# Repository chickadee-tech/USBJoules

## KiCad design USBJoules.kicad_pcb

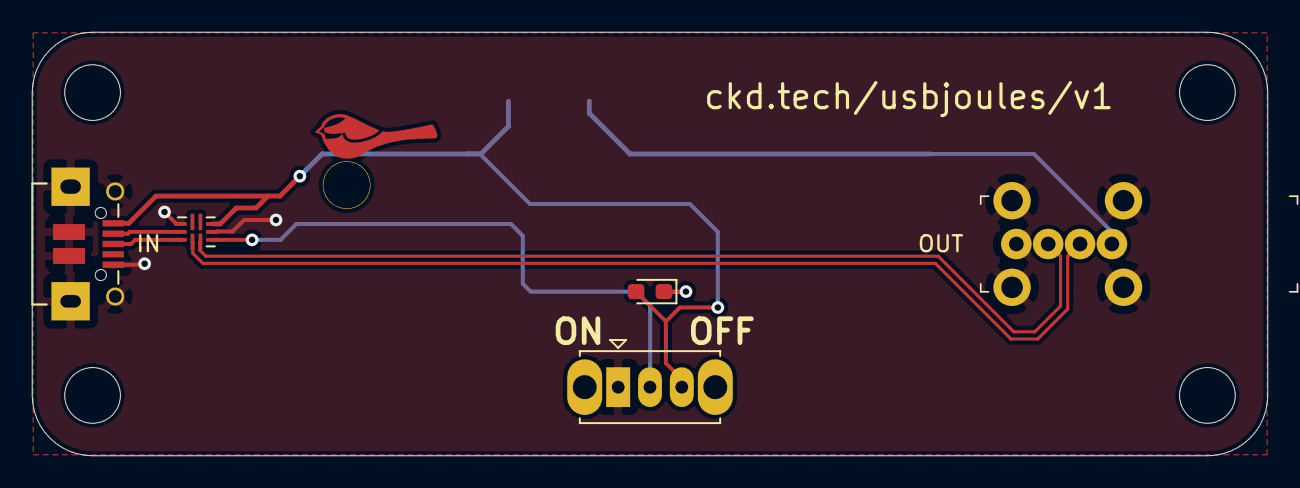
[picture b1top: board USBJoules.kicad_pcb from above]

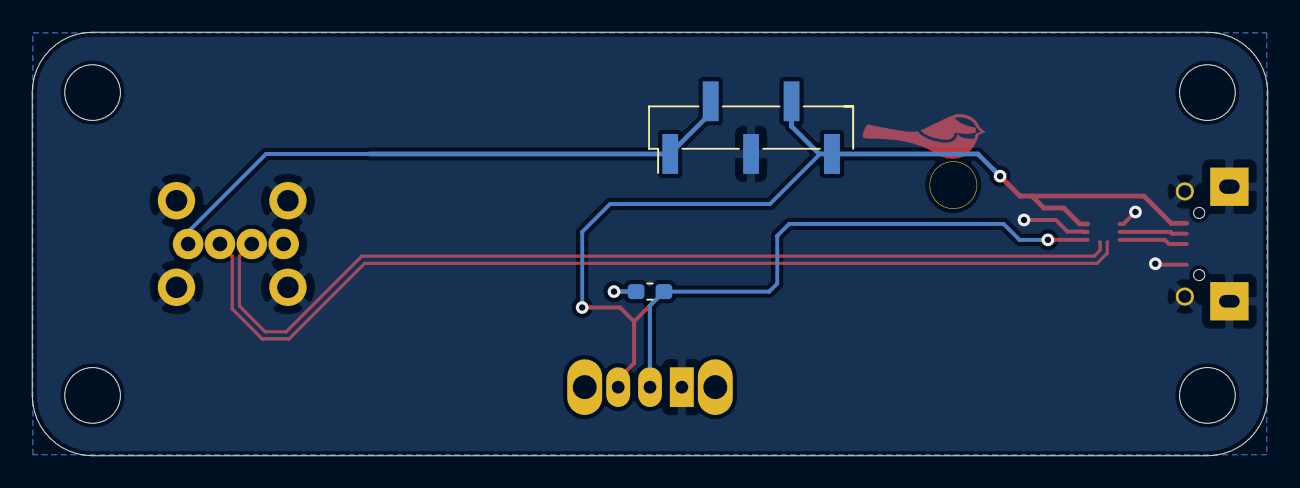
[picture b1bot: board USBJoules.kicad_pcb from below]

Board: 2 copper layers, 77.6 x 26.6 mm, 7 parts (2 on the bottom side), 9 nets.

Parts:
D1: LED; LED_0603_1608Metric_Pad1.05x0.95mm_HandSolder
J1: USB_B_Micro; 4UCONN_20329_V2_USB
J2: Conn_01x05_Male; PinHeader_1x05_P2.54mm_Vertical_SMD_Pin1Left
J3: 73725-0110BLF; USB_A_Female_Vertical_RA_73725-0110BLF
R1: 1k; R_0603_1608Metric_Pad1.05x0.95mm_HandSolder
SW1: SW_SPDT; SW_Slide_1P2T_CK_OS102011MS2Q
U1: USB3740B-AI9; UQFN-10_1.6x2.1mm_P0.5mm

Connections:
+5V: D1.2, J1.1, J2.4, J2.5, SW1.3, U1.5
/EN: R1.2, SW1.2, U1.3
/IN+: J1.3, U1.10
/IN-: J1.2, U1.9
/OUT+: J3.3, U1.2
/OUT-: J3.2, U1.1
GND: J1.5, J1.6, J2.3, J3.4, J3.SH, SW1.1, U1.4, U1.8
unnamed: D1.1, R1.1
VBUS: J2.1, J2.2, J3.1

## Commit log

2021-01-01 v1 for joulescope
